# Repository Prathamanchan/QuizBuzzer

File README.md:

# QuizBuzzer
PCB Project of KarMic

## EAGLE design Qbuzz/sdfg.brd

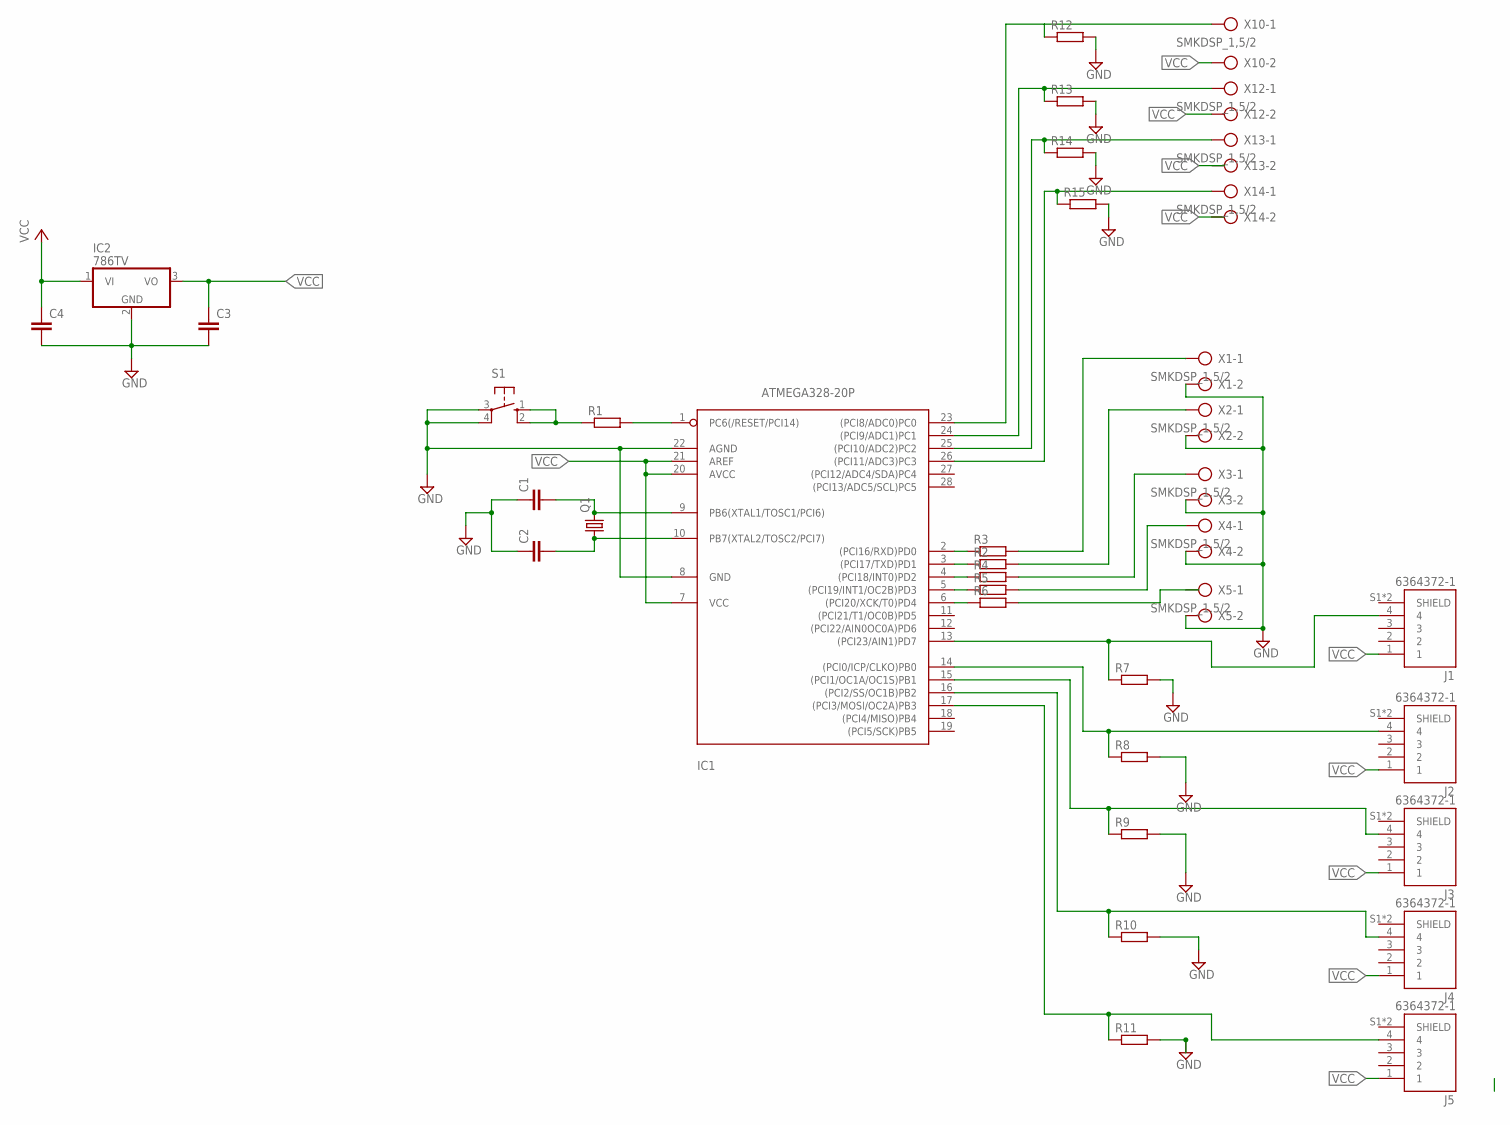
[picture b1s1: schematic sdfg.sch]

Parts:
C1, C2: C-EU025-030X050; C025-030X050
C3, C4: C-EU025-025X050; C025-025X050
IC1: ATMEGA328-20P; DIL28-3
IC2: 786TV; TO220V
J1, J2, J3, J4, J5: 6364372-1; TE_6364372-1
Q1: CRYSTALHC49U70; HC49U70
R1, R2, R3, R4, R5, R6, R7, R8, R9, R10, R11, R12, R13, R14, R15: R-EU_0204/5; 0204/5
S1: 10-XX; B3F-10XX
X1, X2, X3, X4, X5, X10, X12, X13, X14: SMKDSP_1,5/2

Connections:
GND: C1.1, C2.1, C3.2, C4.2, IC1.8 (GND), IC1.22 (AGND), IC2.2 (GND), R7.2, R8.2, R9.2, R10.2, R11.2, R12.2, R13.2, R14.2, R15.2, S1.3, S1.4 (P1), X1.2, X2.2, X3.2, X4.2, X5.2
unnamed: C1.2, IC1.9 (PB6(XTAL1/TOSC1/PCI6)), Q1.2
unnamed: C2.2, IC1.10 (PB7(XTAL2/TOSC2/PCI7)), Q1.1
unnamed: IC1.1 (PC6(/RESET/PCI14)), R1.2
unnamed: R1.1, S1.1 (S), S1.2 (S1)
unnamed: IC1.2 ((PCI16/RXD)PD0), R3.1
unnamed: IC1.3 ((PCI17/TXD)PD1), R2.1
unnamed: IC1.4 ((PCI18/INT0)PD2), R4.1
unnamed: IC1.5 ((PCI19/INT1/OC2B)PD3), R5.1
unnamed: IC1.6 ((PCI20/XCK/T0)PD4), R6.1
unnamed: IC1.13 ((PCI23/AIN1)PD7), J1.4, R7.1
unnamed: IC1.14 ((PCI0/ICP/CLKO)PB0), J2.4, R8.1
unnamed: IC1.15 ((PCI1/OC1A/OC1S)PB1), J3.4, R9.1
unnamed: IC1.16 ((PCI2/SS/OC1B)PB2), J4.4, R10.1
unnamed: IC1.17 ((PCI3/MOSI/OC2A)PB3), J5.4, R11.1
unnamed: R3.2, X1.1
unnamed: R2.2, X2.1
unnamed: R4.2, X3.1
unnamed: R5.2, X4.1
unnamed: IC1.23 ((PCI8/ADC0)PC0), R12.1, X10.1
unnamed: IC1.24 ((PCI9/ADC1)PC1), R13.1, X12.1
unnamed: IC1.25 ((PCI10/ADC2)PC2), R14.1, X13.1
unnamed: IC1.26 ((PCI11/ADC3)PC3), R15.1, X14.1
VCC: C3.1, C4.1, IC1.7 (VCC), IC1.20 (AVCC), IC1.21 (AREF), IC2.1 (VI), IC2.3 (VO), J2.1

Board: 2 copper layers, 37 parts (0 on the bottom side), 24 nets, no tracks yet.

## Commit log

2018-09-11 Hello
